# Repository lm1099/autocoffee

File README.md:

# SDP DT05 - AutoCoffee

## To-do
- Add power headers
- Layout main PCB
- Finish power PCB schematic

## Done
- Voltage regulators (12V to 5V, 3.3V)
- GPIO headers
- HM-10 BLE module
- LCD module
- DS3231 RTC module
- ISCP programming interface
- DS18B20 temp sensors (x2)
- VL6810X TOF sensors (x4)
- A4988 stepper motor drivers (x6)
- Fan driver (x1)

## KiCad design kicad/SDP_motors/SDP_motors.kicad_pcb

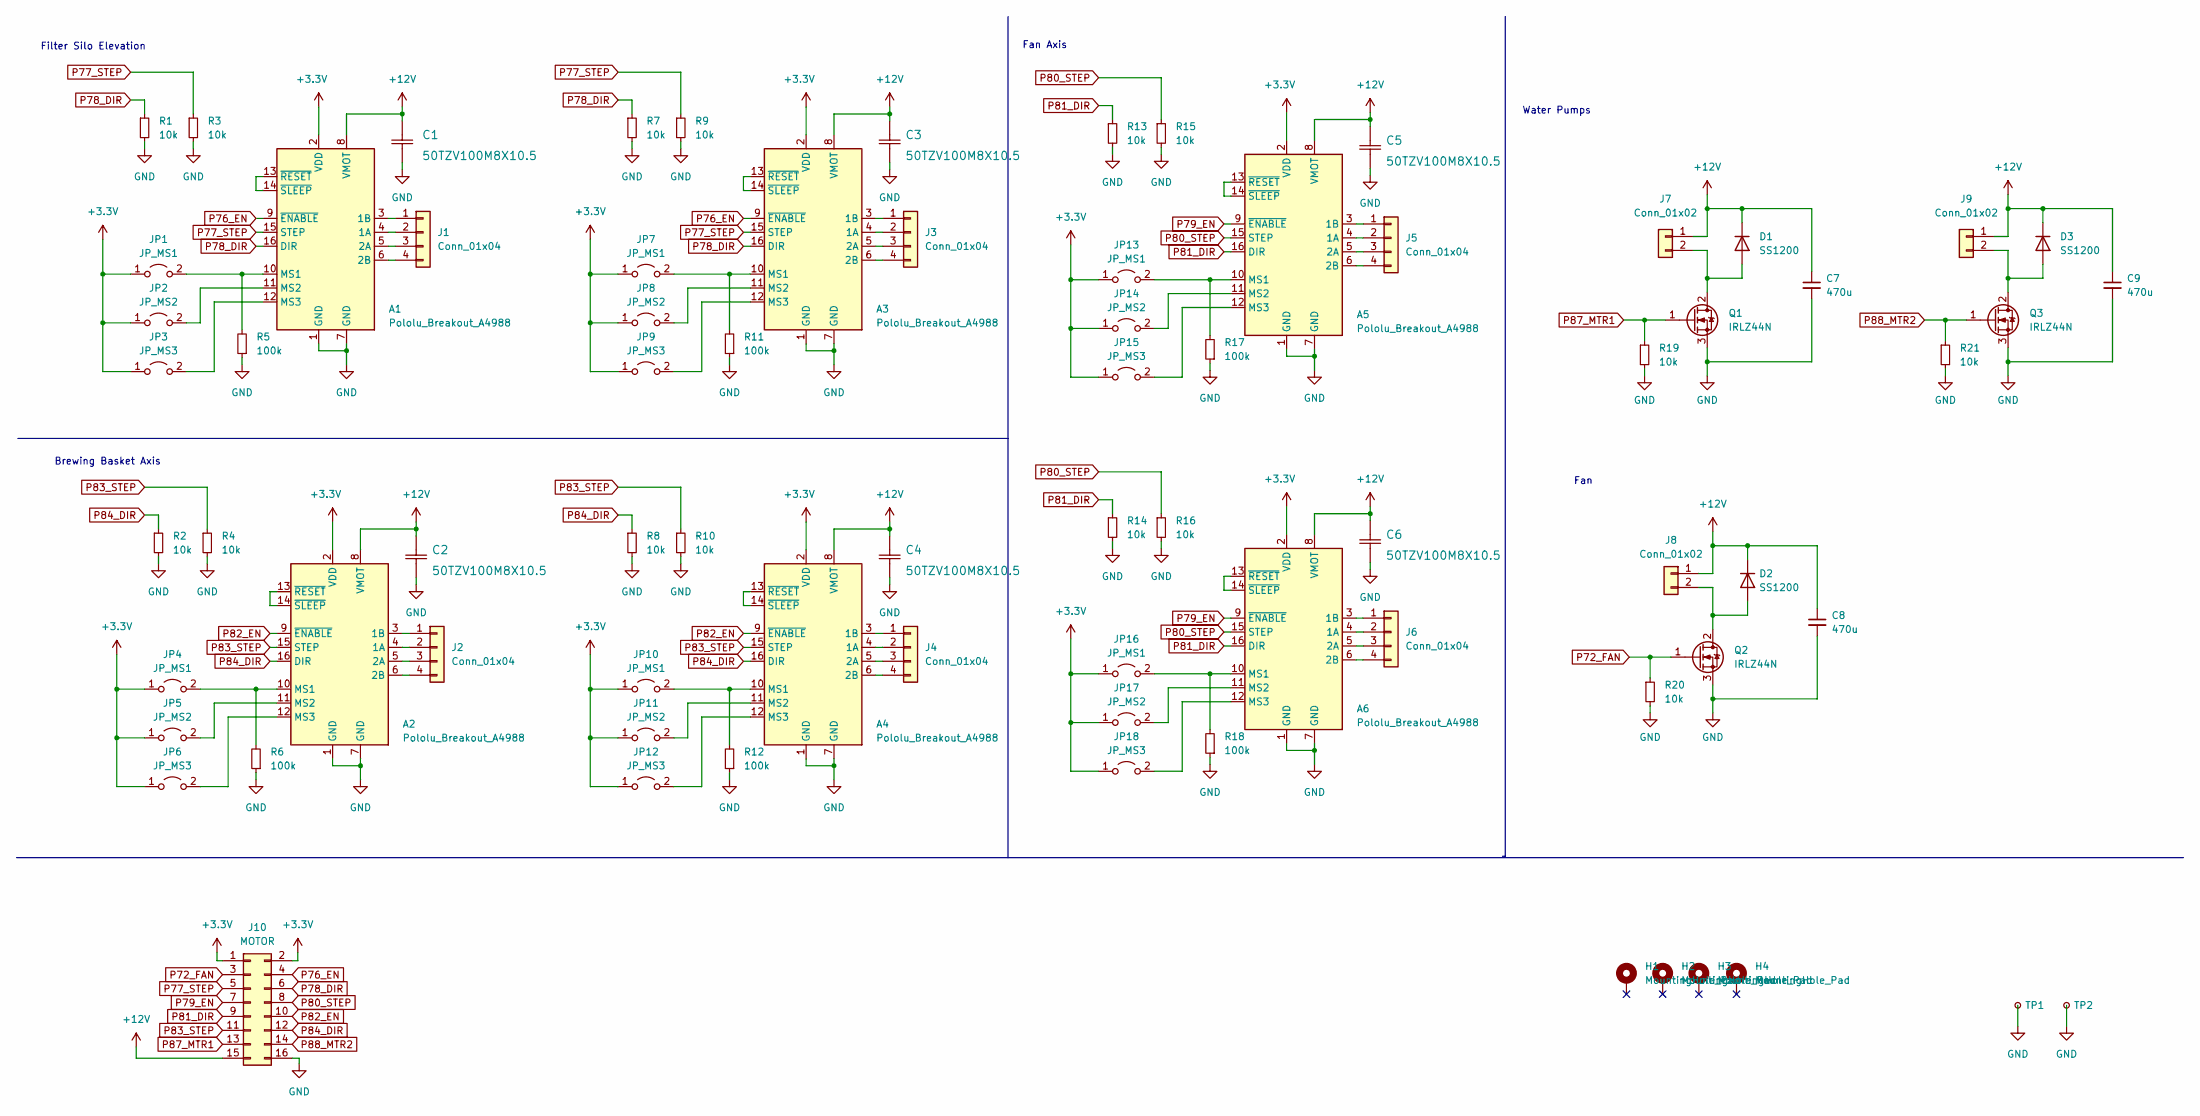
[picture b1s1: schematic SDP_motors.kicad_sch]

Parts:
A1, A2, A3, A4, A5, A6: Pololu_Breakout_A4988; Pololu_Breakout-16_15.2x20.3mm
C1, C2, C3, C4, C5, C6: 50TZV100M8X10.5
C7, C8, C9: 470u; C_Radial_D12.5mm_H20.0mm_P5.00mm
D1, D2, D3: SS1200; D_SMA
H1, H2, H3, H4: MountingHole_Pad; MountingHole_3.2mm_M3_Pad
J1, J2, J3, J4, J5, J6: Conn_01x04; PinHeader_1x04_P2.54mm_Vertical
J7, J8, J9: Conn_01x02; TerminalBlock_Phoenix_PT-1,5-2-5.0-H_1x02_P5.00mm_Horizontal
J10: MOTOR; PinSocket_2x08_P2.54mm_Vertical
JP1, JP4, JP7, JP10, JP13, JP16: JP_MS1; SolderJumper-2_P1.3mm_Open_RoundedPad1.0x1.5mm
JP2, JP5, JP8, JP11, JP14, JP17: JP_MS2; SolderJumper-2_P1.3mm_Open_RoundedPad1.0x1.5mm
JP3, JP6, JP9, JP12, JP15, JP18: JP_MS3; SolderJumper-2_P1.3mm_Open_RoundedPad1.0x1.5mm
Q1, Q2, Q3: IRLZ44N; TO-263-2
R1, R2, R3, R4, R7, R8, R9, R10, R13, R14, R15, R16, R19, R20, R21: 10k; R_0805_2012Metric
R5, R6, R11, R12, R17, R18: 100k; R_0805_2012Metric
TP1, TP2: TestPoint_Small; TestPoint_Keystone_5005-5009_Compact

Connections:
+3V3: A1.2 (VDD), A2.2 (VDD), A3.2 (VDD), A4.2 (VDD), A5.2 (VDD), A6.2 (VDD), J10.1, J10.2, JP1.1 (A), JP2.1 (A), JP3.1 (A), JP4.1 (A), JP5.1 (A), JP6.1 (A), JP7.1 (A), JP8.1 (A), JP9.1 (A), JP10.1 (A), JP11.1 (A), JP12.1 (A), JP13.1 (A), JP14.1 (A), JP15.1 (A), JP16.1 (A), JP17.1 (A), JP18.1 (A)
+12V: A1.8 (VMOT), A2.8 (VMOT), A3.8 (VMOT), A4.8 (VMOT), A5.8 (VMOT), A6.8 (VMOT), C1.2, C2.2, C3.2, C4.2, C5.2, C6.2, C7.1, C8.1, C9.1, D1.1 (K), D2.1 (K), D3.1 (K), J7.1, J8.1, J9.1, J10.15
GND: A1.1 (GND), A1.7 (GND), A2.1 (GND), A2.7 (GND), A3.1 (GND), A3.7 (GND), A4.1 (GND), A4.7 (GND), A5.1 (GND), A5.7 (GND), A6.1 (GND), A6.7 (GND), C1.1, C2.1, C3.1, C4.1, C5.1, C6.1, C7.2, C8.2, C9.2, J10.16, Q1.3 (S), Q2.3 (S), Q3.3 (S), R1.2, R2.2, R3.2, R4.2, R5.1, R6.1, R7.2, R8.2, R9.2, R10.2, R11.1, R12.1, R13.2, R14.2, R15.2, R16.2, R17.1, R18.1, R19.2, R20.2, R21.2, TP1.1, TP2.1
unnamed: A1.3 (1B), J1.1
unnamed: A1.4 (1A), J1.2
unnamed: A1.5 (2A), J1.3
unnamed: A1.6 (2B), J1.4
unnamed: A1.10 (MS1), JP1.2 (B), R5.2
unnamed: A1.11 (MS2), JP2.2 (B)
unnamed: A1.12 (MS3), JP3.2 (B)
unnamed: A1.13 (~RESET), A1.14 (~SLEEP)
unnamed: A2.3 (1B), J2.1
unnamed: A2.4 (1A), J2.2
unnamed: A2.5 (2A), J2.3
unnamed: A2.6 (2B), J2.4
unnamed: A2.10 (MS1), JP4.2 (B), R6.2
unnamed: A2.11 (MS2), JP5.2 (B)
unnamed: A2.12 (MS3), JP6.2 (B)
unnamed: A2.13 (~RESET), A2.14 (~SLEEP)
unnamed: A3.3 (1B), J3.1
unnamed: A3.4 (1A), J3.2
unnamed: A3.5 (2A), J3.3
unnamed: A3.6 (2B), J3.4
unnamed: A3.10 (MS1), JP7.2 (B), R11.2
unnamed: A3.11 (MS2), JP8.2 (B)
unnamed: A3.12 (MS3), JP9.2 (B)
unnamed: A3.13 (~RESET), A3.14 (~SLEEP)
unnamed: A4.3 (1B), J4.1
unnamed: A4.4 (1A), J4.2
unnamed: A4.5 (2A), J4.3
unnamed: A4.6 (2B), J4.4
unnamed: A4.10 (MS1), JP10.2 (B), R12.2
unnamed: A4.11 (MS2), JP11.2 (B)
unnamed: A4.12 (MS3), JP12.2 (B)
unnamed: A4.13 (~RESET), A4.14 (~SLEEP)
unnamed: A5.3 (1B), J5.1
unnamed: A5.4 (1A), J5.2
unnamed: A5.5 (2A), J5.3
unnamed: A5.6 (2B), J5.4
unnamed: A5.10 (MS1), JP13.2 (B), R17.2
unnamed: A5.11 (MS2), JP14.2 (B)
unnamed: A5.12 (MS3), JP15.2 (B)
unnamed: A5.13 (~RESET), A5.14 (~SLEEP)
unnamed: A6.3 (1B), J6.1
unnamed: A6.4 (1A), J6.2
unnamed: A6.5 (2A), J6.3
unnamed: A6.6 (2B), J6.4
unnamed: A6.10 (MS1), JP16.2 (B), R18.2
unnamed: A6.11 (MS2), JP17.2 (B)
unnamed: A6.12 (MS3), JP18.2 (B)
unnamed: A6.13 (~RESET), A6.14 (~SLEEP)
unnamed: D1.2 (A), J7.2, Q1.2 (D)
unnamed: D2.2 (A), J8.2, Q2.2 (D)
unnamed: D3.2 (A), J9.2, Q3.2 (D)
P72_FAN: J10.3, Q2.1 (G), R20.1
P76_EN: A1.9 (~ENABLE), A3.9 (~ENABLE), J10.4
P77_STEP: A1.15 (STEP), A3.15 (STEP), J10.5, R3.1, R9.1
P78_DIR: A1.16 (DIR), A3.16 (DIR), J10.6, R1.1, R7.1
P79_EN: A5.9 (~ENABLE), A6.9 (~ENABLE), J10.7
P80_STEP: A5.15 (STEP), A6.15 (STEP), J10.8, R15.1, R16.1
P81_DIR: A5.16 (DIR), A6.16 (DIR), J10.9, R13.1, R14.1
P82_EN: A2.9 (~ENABLE), A4.9 (~ENABLE), J10.10
P83_STEP: A2.15 (STEP), A4.15 (STEP), J10.11, R4.1, R10.1
P84_DIR: A2.16 (DIR), A4.16 (DIR), J10.12, R2.1, R8.1
P87_MTR1: J10.13, Q1.1 (G), R19.1
P88_MTR2: J10.14, Q3.1 (G), R21.1

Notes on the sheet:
Filter Silo Elevation
Water Pumps
Fan
Brewing Basket Axis
Fan Axis

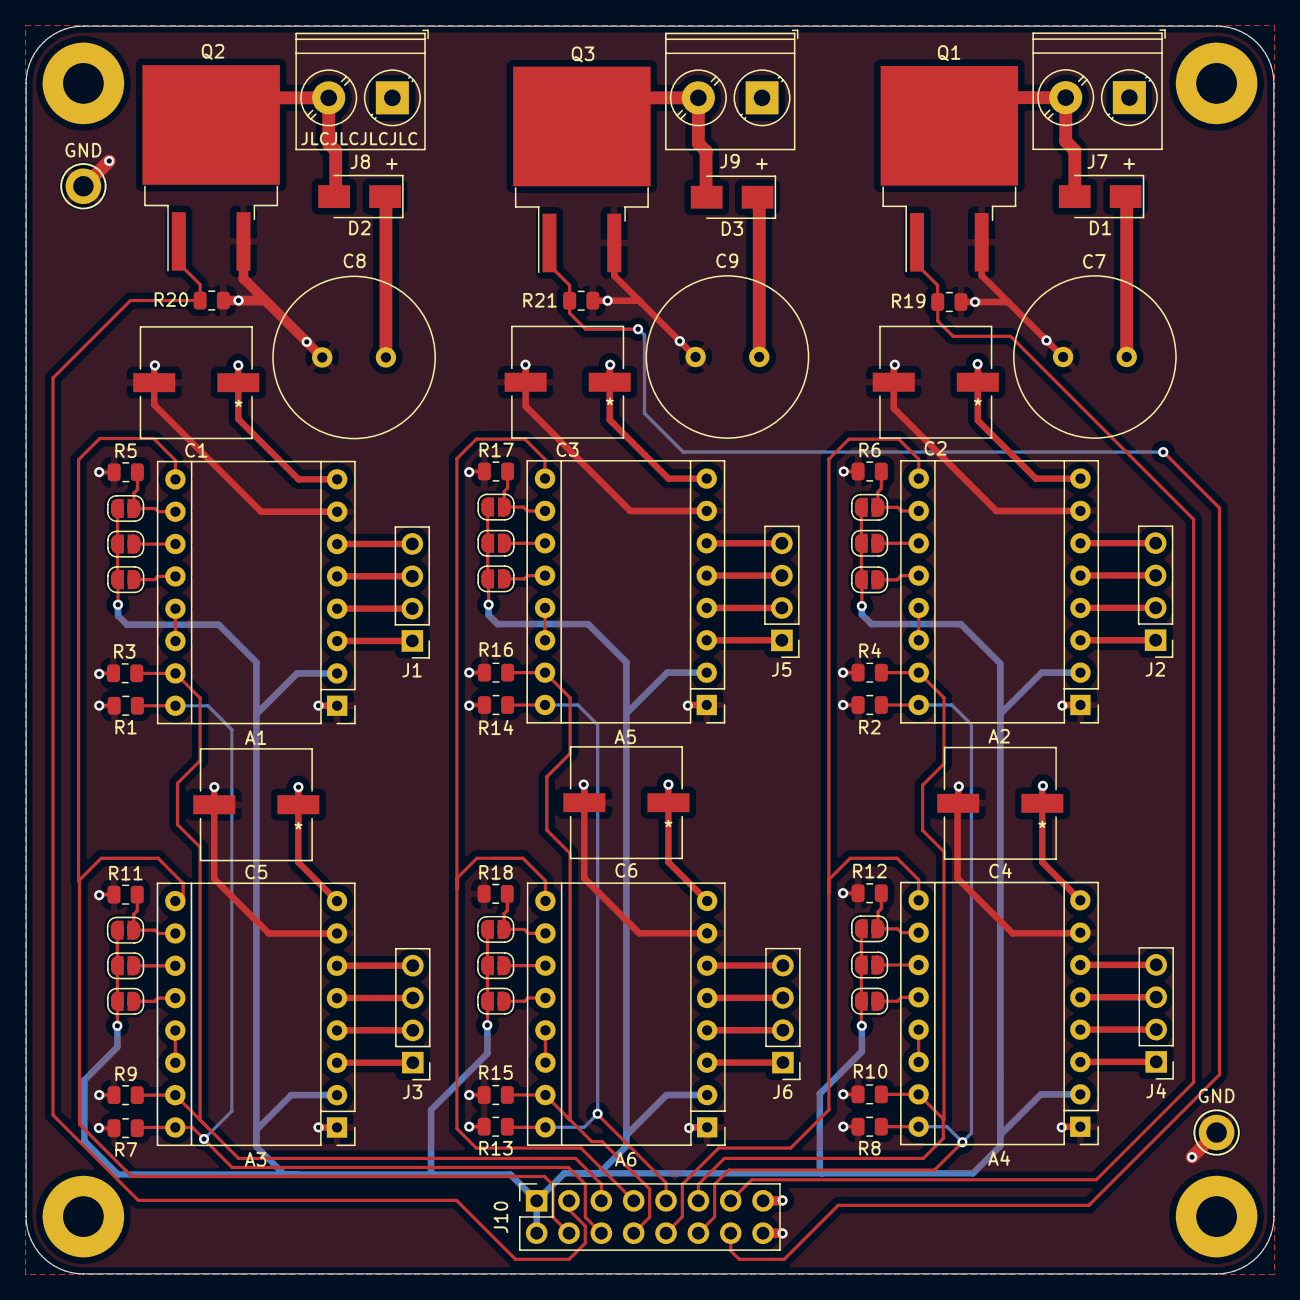
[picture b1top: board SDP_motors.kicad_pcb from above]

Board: 4 copper layers, 98.0 x 98.0 mm, 76 parts (0 on the bottom side), 66 nets.

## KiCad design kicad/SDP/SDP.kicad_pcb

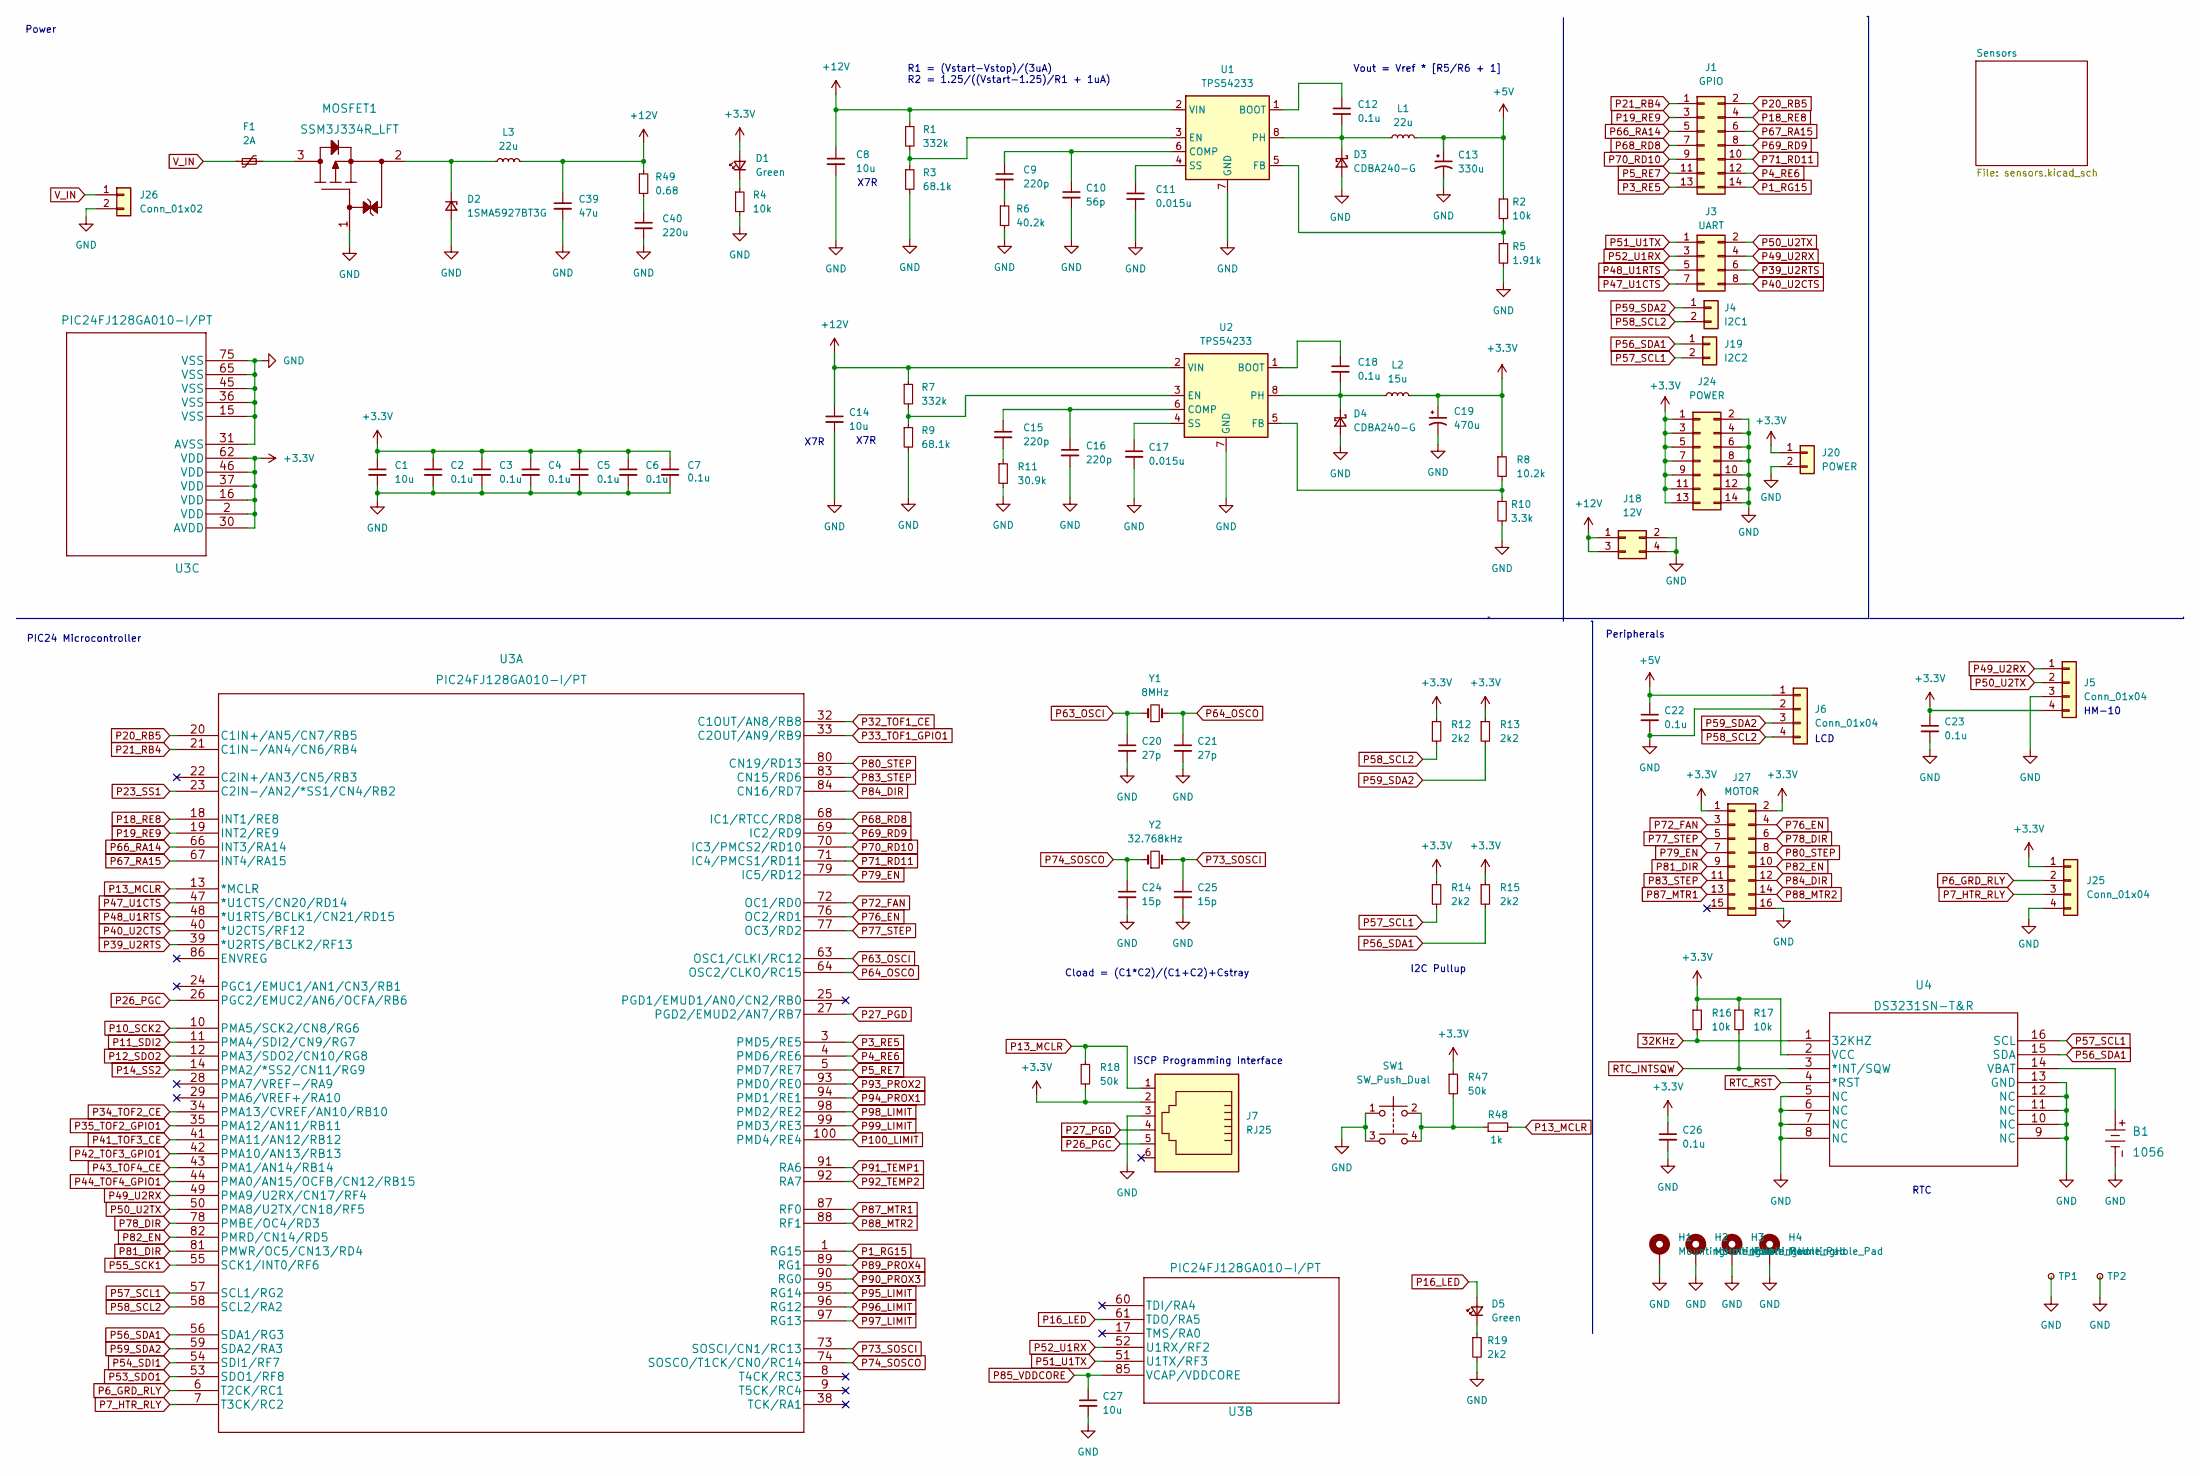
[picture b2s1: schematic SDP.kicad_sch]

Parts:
B1: 1056
C1, C27: 10u; C_0805_2012Metric
C2, C3, C4, C5, C6, C7: 0.1u; C_0603_1608Metric
C8, C14: 10u; C_1206_3216Metric
C9, C15, C16: 220p; C_0805_2012Metric
C10: 56p; C_0805_2012Metric
C11, C17: 0.015u; C_0805_2012Metric
C12, C18, C22, C23, C26: 0.1u; C_0805_2012Metric
C13: 330u; EEETG1C331UP
C19: 470u; EEVTG1C471Q
C20, C21: 27p; C_0805_2012Metric
C24, C25: 15p; C_0805_2012Metric
C39: 47u; C_Radial_D8.0mm_H11.5mm_P3.50mm
C40: 220u; C_Radial_D10.0mm_H16.0mm_P5.00mm
D1, D5: Green; LED_0805_2012Metric
D2: 1SMA5927BT3G; D_SMA
D3, D4: CDBA240-G; D_SMA
F1: 2A; Fuse_1206_3216Metric
H1, H2, H3, H4: MountingHole_Pad; MountingHole_3.2mm_M3_Pad
J1: GPIO; PinSocket_2x07_P2.54mm_Vertical
J3: UART; PinSocket_2x04_P2.54mm_Vertical
J4: I2C1; PinSocket_1x02_P2.54mm_Vertical
J5, J6, J25: Conn_01x04; PinSocket_1x04_P2.54mm_Vertical
J7: RJ25; TE_5555165-1
J18: 12V; PinSocket_2x02_P2.54mm_Vertical
J19: I2C2; PinSocket_1x02_P2.54mm_Vertical
J20: POWER; PinSocket_1x02_P2.54mm_Vertical
J24: POWER; PinSocket_2x07_P2.54mm_Vertical
J26: Conn_01x02; TerminalBlock_Phoenix_PT-1,5-2-5.0-H_1x02_P5.00mm_Horizontal
J27: MOTOR; PinSocket_2x08_P2.54mm_Vertical
L1, L3: 22u; DR125-220-R
L2: 15u; L_12x12mm_H8mm
MOSFET1: SSM3J334R_LFT; SOT-23
R1, R7: 332k; R_0805_2012Metric
R2, R4, R16, R17: 10k; R_0805_2012Metric
R3, R9: 68.1k; R_0805_2012Metric
R5: 1.91k; R_0805_2012Metric
R6: 40.2k; R_0805_2012Metric
R8: 10.2k; R_0805_2012Metric
R10: 3.3k; R_0805_2012Metric
R11: 30.9k; R_0805_2012Metric
R12, R13, R14, R15, R19: 2k2; R_0805_2012Metric
R18, R47: 50k; R_0805_2012Metric
R48: 1k; R_0805_2012Metric
R49: 0.68; R_0805_2012Metric
SW1: SW_Push_Dual; SW_1825910-6-4
TP1, TP2: TestPoint_Small; TestPoint_Keystone_5005-5009_Compact
U1, U2: TPS54233; SOIC-8_3.9x4.9mm_P1.27mm
U3: PIC24FJ128GA010-I/PT; PIC24FJ128GA010-I&slash_PT
U4: DS3231SN-T&R
Y1: 8MHz; XTAL_ECS-80-20-5PXDU-TR
Y2: 32.768kHz; Crystal_DS26_D2.0mm_L6.0mm_Horizontal

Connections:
32KHz: R16.2, U4.1 (32KHZ)
+3V3: C1.1, C2.1, C3.1, C4.1, C5.1, C6.1, C7.1, C19.1, C23.1, C26.1, D1.2 (A), J5.4, J7.2, J20.1, J24.1, J24.3, J24.5, J24.7, J24.9, J24.11, J24.13, J25.1, J27.1, J27.2, L2.2, R8.1, R12.1, R13.1, R14.1, R15.1, R16.1, R17.1, R18.2, R47.1, U3.2 (VDD), U3.16 (VDD), U3.30 (AVDD), U3.37 (VDD), U3.46 (VDD), U3.62 (VDD), U4.2 (VCC); also elsewhere on the board
+5V: C13.1, C22.1, J6.1, L1.2, R2.1
+12V: C8.1, C14.1, C39.1, J18.1, J18.3, L3.2, R1.1, R7.1, R49.1, U1.2 (VIN), U2.2 (VIN)
GND: B1.1, C1.2, C2.2, C3.2, C4.2, C5.2, C6.2, C7.2, C8.2, C10.2, C11.2, C13.2, C14.2, C16.2, C17.2, C19.2, C20.2, C21.2, C22.2, C23.2, C24.2, C25.2, C26.2, C27.2, C39.2, C40.2, D2.2 (A), D3.2 (A), D4.2 (A), H1.1, H2.1, H3.1, H4.1, J5.3, J6.2, J7.3, J18.2, J18.4, J20.2, J24.2, J24.4, J24.6, J24.8, J24.10, J24.12, J24.14, J25.4, J26.2, J27.16, MOSFET1.1 (GATE), R3.2, R4.2, R5.2, R6.2, R9.2, R10.2, R11.2, R19.2, SW1.1, SW1.3, TP1.1, TP2.1, U1.7 (GND), U2.7 (GND), U3.15 (VSS), U3.31 (AVSS), U3.36 (VSS), U3.45 (VSS), U3.65 (VSS), U3.75 (VSS), U4.5 (NC), U4.6 (NC), U4.7 (NC), U4.8 (NC), U4.9 (NC), U4.10 (NC), U4.11 (NC), U4.12 (NC), U4.13 (GND); also elsewhere on the board
unnamed: B1.2, U4.14 (VBAT)
unnamed: C9.2, R6.1
unnamed: C9.1, C10.1, U1.6 (COMP)
unnamed: C11.1, U1.4 (SS)
unnamed: C12.1, U1.1 (BOOT)
unnamed: C12.2, D3.1 (K), L1.1, U1.8 (PH)
unnamed: C15.1, C16.1, U2.6 (COMP)
unnamed: C15.2, R11.1
unnamed: C17.1, U2.4 (SS)
unnamed: C18.1, U2.1 (BOOT)
unnamed: C18.2, D4.1 (K), L2.1, U2.8 (PH)
unnamed: C40.1, R49.2
unnamed: D1.1 (K), R4.1
unnamed: D2.1 (K), L3.1, MOSFET1.2 (SOURCE)
unnamed: D5.1 (K), R19.1
unnamed: F1.2, MOSFET1.3 (DRAIN)
unnamed: R1.2, R3.1, U1.3 (EN)
unnamed: R2.2, R5.1, U1.5 (FB)
unnamed: R7.2, R9.1, U2.3 (EN)
unnamed: R8.2, R10.1, U2.5 (FB)
unnamed: R47.2, R48.1, SW1.2, SW1.4
P1_RG15: J1.14, U3.1 (RG15)
P3_RE5: J1.13, U3.3 (PMD5/RE5)
P4_RE6: J1.12, U3.4 (PMD6/RE6)
P5_RE7: J1.11, U3.5 (PMD7/RE7)
P6_GRD_RLY: J25.2, U3.6 (T2CK/RC1)
P7_HTR_RLY: J25.3, U3.7 (T3CK/RC2)
P10_SCK2: U3.10 (PMA5/SCK2/CN8/RG6)
P11_SDI2: U3.11 (PMA4/SDI2/CN9/RG7)
P12_SDO2: U3.12 (PMA3/SDO2/CN10/RG8)
P13_MCLR: J7.1, R18.1, R48.2, U3.13 (*MCLR)
P14_SS2: U3.14 (PMA2/*SS2/CN11/RG9)
P16_LED: D5.2 (A), U3.61 (TDO/RA5)
P18_RE8: J1.4, U3.18 (INT1/RE8)
P19_RE9: J1.3, U3.19 (INT2/RE9)
P20_RB5: J1.2, U3.20 (C1IN+/AN5/CN7/RB5)
P21_RB4: J1.1, U3.21 (C1IN-/AN4/CN6/RB4)
P23_SS1: U3.23 (C2IN-/AN2/*SS1/CN4/RB2)
P26_PGC: J7.5, U3.26 (PGC2/EMUC2/AN6/OCFA/RB6)
P27_PGD: J7.4, U3.27 (PGD2/EMUD2/AN7/RB7)
P32_TOF1_CE: U3.32 (C1OUT/AN8/RB8); also elsewhere on the board
P33_TOF1_GPIO1: U3.33 (C2OUT/AN9/RB9); also elsewhere on the board
P34_TOF2_CE: U3.34 (PMA13/CVREF/AN10/RB10); also elsewhere on the board
P35_TOF2_GPIO1: U3.35 (PMA12/AN11/RB11); also elsewhere on the board
P39_U2RTS: J3.6, U3.39 (*U2RTS/BCLK2/RF13)
P40_U2CTS: J3.8, U3.40 (*U2CTS/RF12)
P41_TOF3_CE: U3.41 (PMA11/AN12/RB12); also elsewhere on the board
P42_TOF3_GPIO1: U3.42 (PMA10/AN13/RB13); also elsewhere on the board
P43_TOF4_CE: U3.43 (PMA1/AN14/RB14); also elsewhere on the board
P44_TOF4_GPIO1: U3.44 (PMA0/AN15/OCFB/CN12/RB15); also elsewhere on the board
P47_U1CTS: J3.7, U3.47 (*U1CTS/CN20/RD14)
P48_U1RTS: J3.5, U3.48 (*U1RTS/BCLK1/CN21/RD15)
P49_U2RX: J3.4, J5.1, U3.49 (PMA9/U2RX/CN17/RF4)
P50_U2TX: J3.2, J5.2, U3.50 (PMA8/U2TX/CN18/RF5)
P51_U1TX: J3.1, U3.51 (U1TX/RF3)
P52_U1RX: J3.3, U3.52 (U1RX/RF2)
P53_SDO1: U3.53 (SDO1/RF8)
P54_SDI1: U3.54 (SDI1/RF7)
P55_SCK1: U3.55 (SCK1/INT0/RF6)
P56_SDA1: J19.1, R15.2, U3.56 (SDA1/RG3), U4.15 (SDA); also elsewhere on the board
P57_SCL1: J19.2, R14.2, U3.57 (SCL1/RG2), U4.16 (SCL); also elsewhere on the board
P58_SCL2: J4.2, J6.4, R12.2, U3.58 (SCL2/RA2); also elsewhere on the board
P59_SDA2: J4.1, J6.3, R13.2, U3.59 (SDA2/RA3); also elsewhere on the board
P63_OSCI: C20.1, U3.63 (OSC1/CLKI/RC12), Y1.1
P64_OSCO: C21.1, U3.64 (OSC2/CLKO/RC15), Y1.2
P66_RA14: J1.5, U3.66 (INT3/RA14)
P67_RA15: J1.6, U3.67 (INT4/RA15)
P68_RD8: J1.7, U3.68 (IC1/RTCC/RD8)
P69_RD9: J1.8, U3.69 (IC2/RD9)
P70_RD10: J1.9, U3.70 (IC3/PMCS2/RD10)
P71_RD11: J1.10, U3.71 (IC4/PMCS1/RD11)
P72_FAN: J27.3, U3.72 (OC1/RD0)
P73_SOSCI: C25.1, U3.73 (SOSCI/CN1/RC13), Y2.2
P74_SOSCO: C24.1, U3.74 (SOSCO/T1CK/CN0/RC14), Y2.1
P76_EN: J27.4, U3.76 (OC2/RD1)
P77_STEP: J27.5, U3.77 (OC3/RD2)
P78_DIR: J27.6, U3.78 (PMBE/OC4/RD3)
P79_EN: J27.7, U3.79 (IC5/RD12)
P80_STEP: J27.8, U3.80 (CN19/RD13)
P81_DIR: J27.9, U3.81 (PMWR/OC5/CN13/RD4)
P82_EN: J27.10, U3.82 (PMRD/CN14/RD5)
P83_STEP: J27.11, U3.83 (CN15/RD6)
P84_DIR: J27.12, U3.84 (CN16/RD7)
P85_VDDCORE: C27.1, U3.85 (VCAP/VDDCORE)
P87_MTR1: J27.13, U3.87 (RF0)
P88_MTR2: J27.14, U3.88 (RF1)
P89_PROX4: U3.89 (RG1); also elsewhere on the board
P90_PROX3: U3.90 (RG0); also elsewhere on the board
P91_TEMP1: U3.91 (RA6); also elsewhere on the board
P92_TEMP2: U3.92 (RA7); also elsewhere on the board
P93_PROX2: U3.93 (PMD0/RE0); also elsewhere on the board
P94_PROX1: U3.94 (PMD1/RE1); also elsewhere on the board
P95_LIMIT: U3.95 (RG14); also elsewhere on the board
P96_LIMIT: U3.96 (RG12); also elsewhere on the board
P97_LIMIT: U3.97 (RG13); also elsewhere on the board
P98_LIMIT: U3.98 (PMD2/RE2); also elsewhere on the board
P99_LIMIT: U3.99 (PMD3/RE3); also elsewhere on the board
P100_LIMIT: U3.100 (PMD4/RE4); also elsewhere on the board
RTC_INTSQW: R17.2, U4.3 (*INT/SQW)
RTC_RST: U4.4 (*RST)
V_IN: F1.1, J26.1

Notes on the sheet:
RTC
X7R
HM-10
Peripherals
R1 = (Vstart-Vstop)/(3uA) R2 = 1.25/((Vstart-1.25)/R1 + 1uA)
I2C Pullup
ISCP Programming Interface
Power
Cload = (C1*C2)/(C1+C2)+Cstray
LCD
PIC24 Microcontroller
Vout = Vref * [R5/R6 + 1]

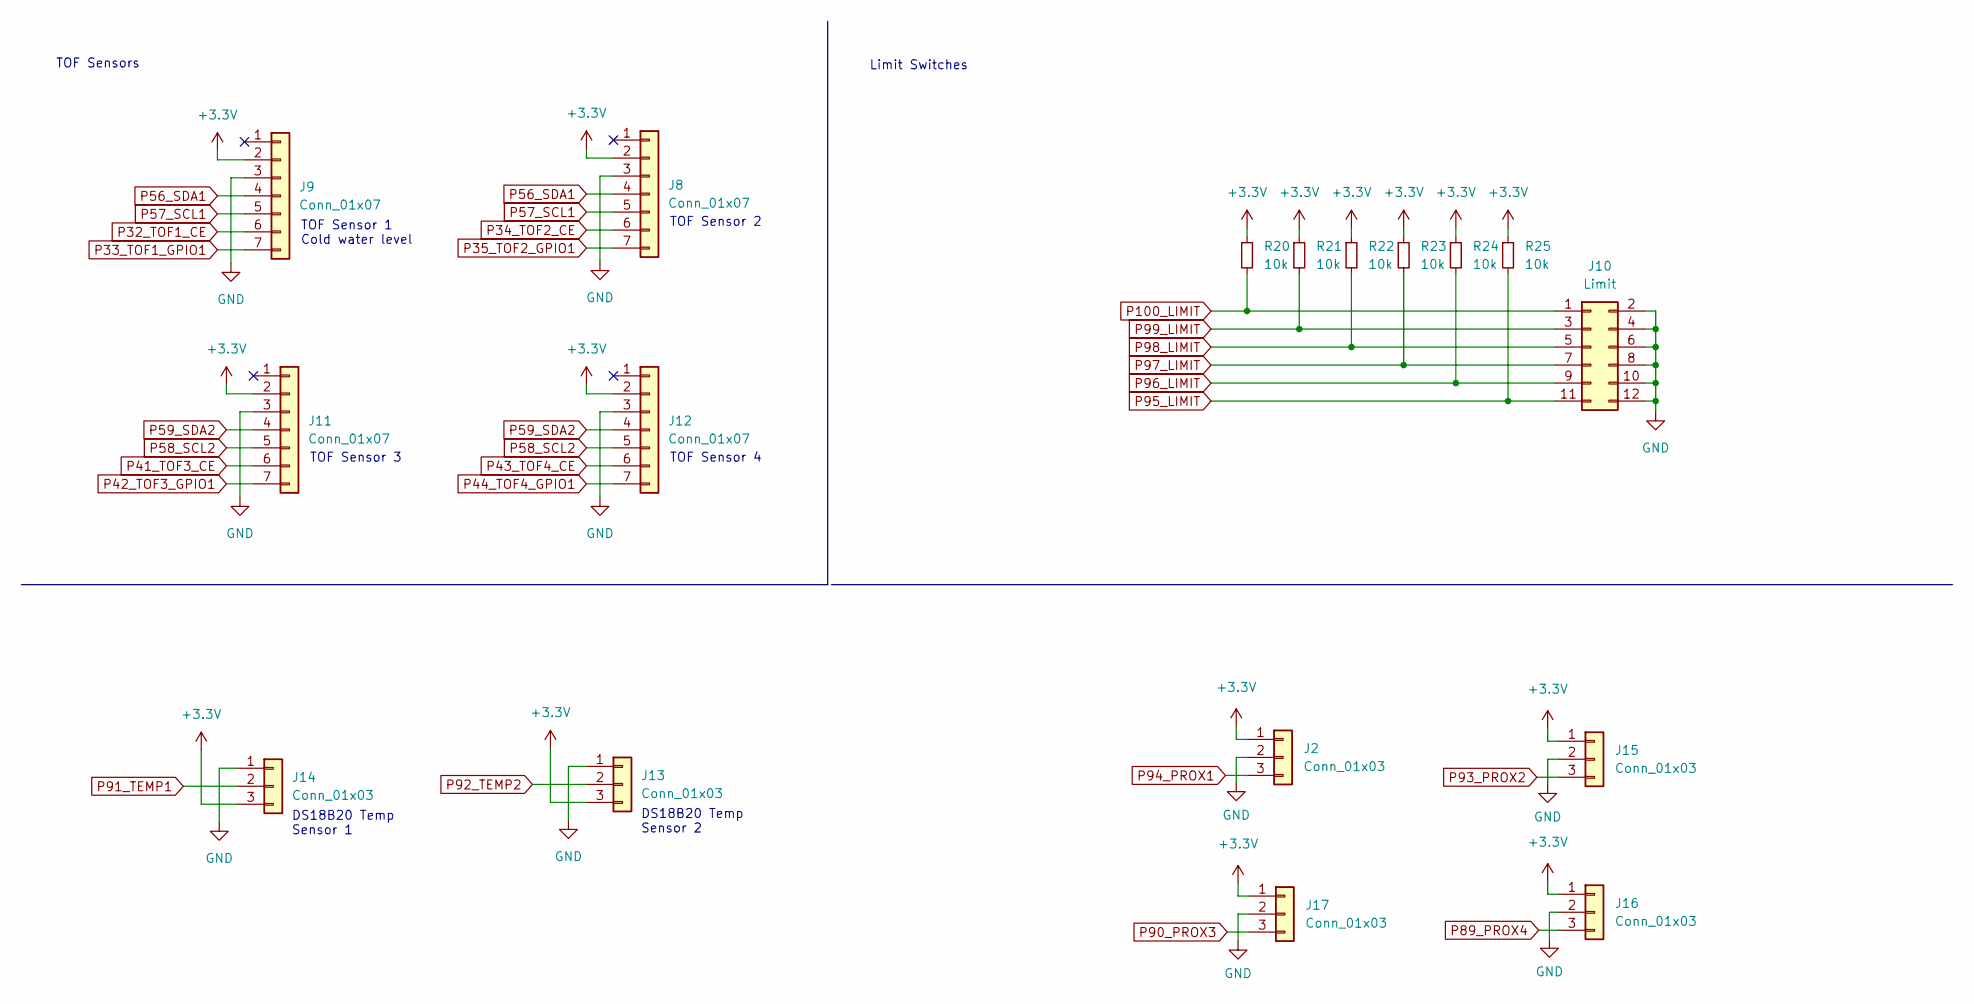
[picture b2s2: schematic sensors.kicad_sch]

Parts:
J2, J13, J14, J15, J16, J17: Conn_01x03; PinSocket_1x03_P2.54mm_Vertical
J8, J9, J11, J12: Conn_01x07; PinSocket_1x07_P2.54mm_Vertical
J10: Limit; PinHeader_2x06_P2.54mm_Vertical
R20, R21, R22, R23, R24, R25: 10k; R_0805_2012Metric

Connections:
+3V3: J2.1, J8.2, J9.2, J11.2, J12.2, J13.3, J14.3, J15.1, J16.1, J17.1, R20.1, R21.1, R22.1, R23.1, R24.1, R25.1; also elsewhere on the board
GND: J2.2, J8.3, J9.3, J10.2, J10.4, J10.6, J10.8, J10.10, J10.12, J11.3, J12.3, J13.1, J14.1, J15.2, J16.2, J17.2; also elsewhere on the board
P32_TOF1_CE: J9.6; also elsewhere on the board
P33_TOF1_GPIO1: J9.7; also elsewhere on the board
P34_TOF2_CE: J8.6; also elsewhere on the board
P35_TOF2_GPIO1: J8.7; also elsewhere on the board
P41_TOF3_CE: J11.6; also elsewhere on the board
P42_TOF3_GPIO1: J11.7; also elsewhere on the board
P43_TOF4_CE: J12.6; also elsewhere on the board
P44_TOF4_GPIO1: J12.7; also elsewhere on the board
P56_SDA1: J8.4, J9.4; also elsewhere on the board
P57_SCL1: J8.5, J9.5; also elsewhere on the board
P58_SCL2: J11.5, J12.5; also elsewhere on the board
P59_SDA2: J11.4, J12.4; also elsewhere on the board
P89_PROX4: J16.3; also elsewhere on the board
P90_PROX3: J17.3; also elsewhere on the board
P91_TEMP1: J14.2; also elsewhere on the board
P92_TEMP2: J13.2; also elsewhere on the board
P93_PROX2: J15.3; also elsewhere on the board
P94_PROX1: J2.3; also elsewhere on the board
P95_LIMIT: J10.11, R25.2; also elsewhere on the board
P96_LIMIT: J10.9, R24.2; also elsewhere on the board
P97_LIMIT: J10.7, R23.2; also elsewhere on the board
P98_LIMIT: J10.5, R22.2; also elsewhere on the board
P99_LIMIT: J10.3, R21.2; also elsewhere on the board
P100_LIMIT: J10.1, R20.2; also elsewhere on the board

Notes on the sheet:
TOF Sensor 4
TOF Sensors
TOF Sensor 1 Cold water level
TOF Sensor 2
TOF Sensor 3
DS18B20 Temp Sensor 2
DS18B20 Temp Sensor 1
Limit Switches

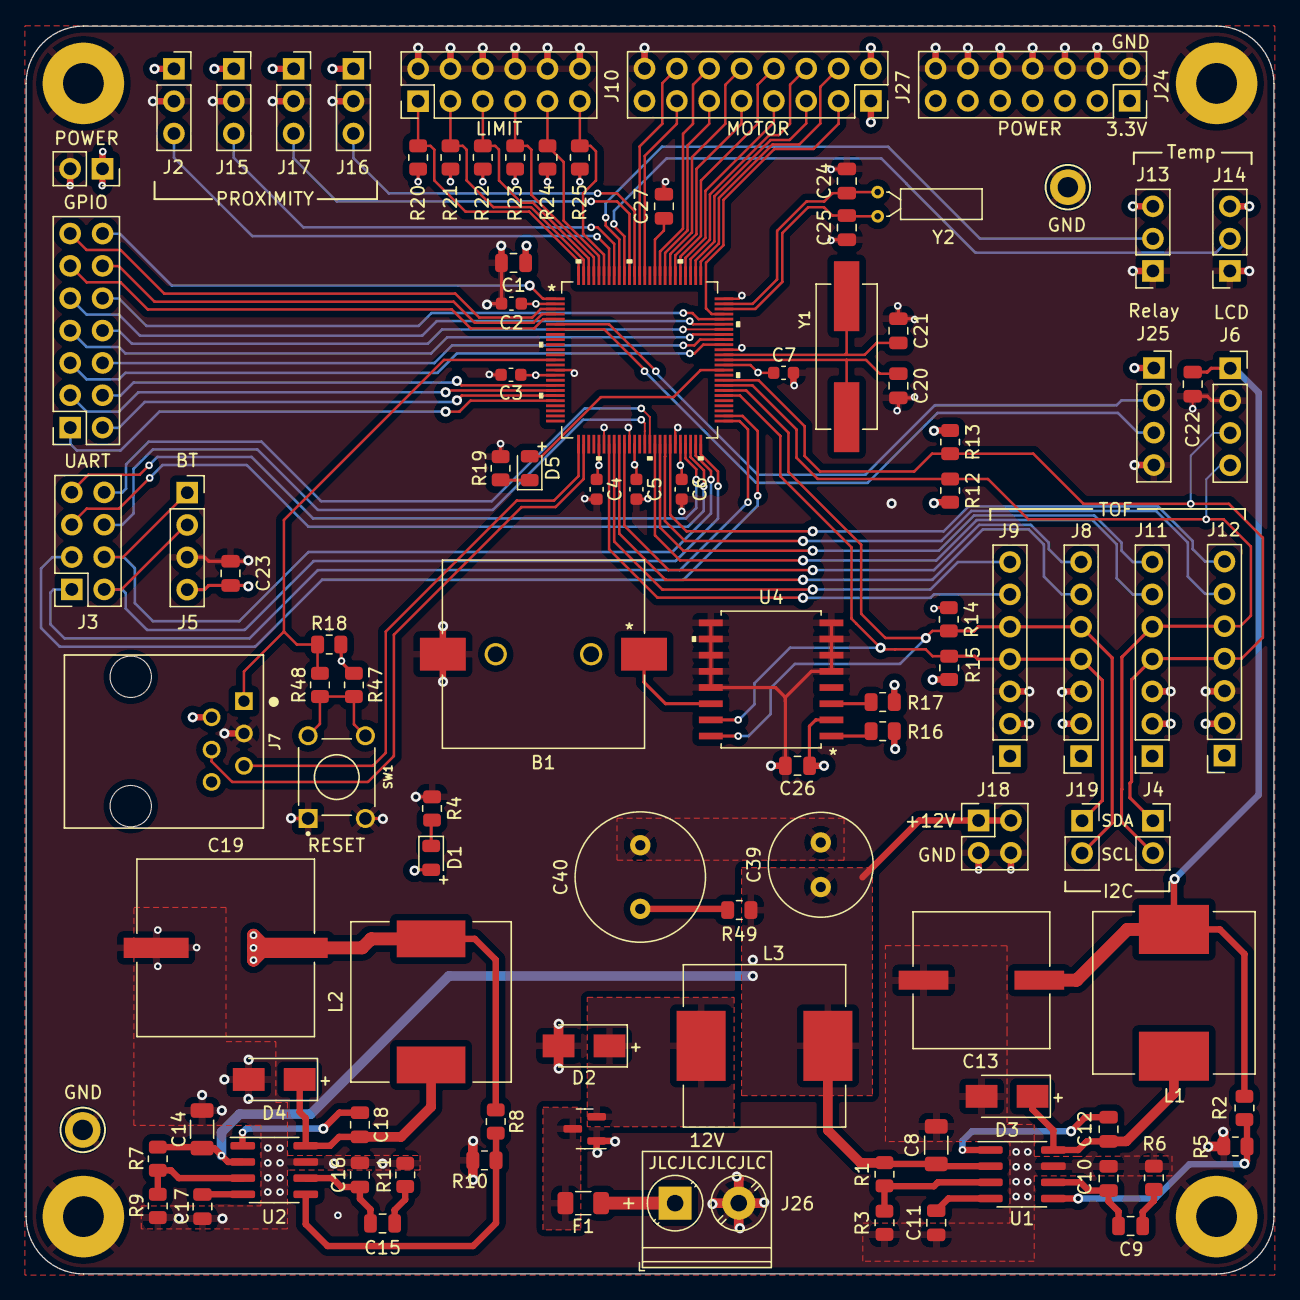
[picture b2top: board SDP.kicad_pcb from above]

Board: 4 copper layers, 98.0 x 98.0 mm, 105 parts (0 on the bottom side), 97 nets.

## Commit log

2022-01-26 original files
2022-01-26 Removed unneeded files
2022-01-26 Restructured
2022-01-26 Added PIC24 and added initial supporting hardware
2022-01-27 Added stepper motor driver
2022-01-27 PIC24 pins
2022-01-27 Added sheet
2022-01-27 Added datasheets and schematics
2022-01-28 Updated schematics
2022-02-03 Added DS3231 RTC and HM-10 BLE module
2022-02-04 Added 5V and 3.3V voltage regulators
2022-02-04 Updated power section
2022-02-04 Updated power requirement estimates
2022-02-05 Added GPIO headers, separated power PCB
2022-02-05 Updated pin assignments
2022-02-05 Updated power estimates
2022-02-07 Part selection
2022-02-08 Added footprints
2022-02-09 Assigned footprints, added limit switches, rearranged schematics
2022-02-10 Assigned footprints and removed ferrite bead
2022-02-10 Deleted test file
2022-02-10 Initial firmware commit
2022-02-10 Added MCLR pullup and assigned footprints
2022-02-10 Updated TODO
2022-02-10 Added input filter and power headers
2022-02-13 PCB layout and footprint assignment fix
2022-02-14 PCB layout and schematic updates
2022-02-14 Added limit switches
2022-02-14 Separated control and motor boards
2022-02-16 PCB layout of main controller board
2022-02-16 Controller PCB layout
2022-02-17 Modified TOF sensor pins
2022-02-18 Added proximity sensor headers
2022-02-21 Motor PCB layout
2022-02-21 Controller and motor PCB silkscreen and final layout
2022-02-21 Ignore MPLab private.xml
2022-02-21 Stop tracking private.xml
2022-02-24 Final PCB layout changes
2022-03-03 Added proximity sensor pins

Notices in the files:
parts and their libraries:
Copyright 2021 Accelerated Designs. All rights reserved.
